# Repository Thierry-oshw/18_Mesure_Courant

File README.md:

# 18_Mesure_Courant
 Mesure courant 

Le module Mesure_courant permet de mesurer un courant sur circuit alternatif ou continu.
La tension sur la broche Imes est proportionnelle au courrant consommé par le circuit à raison de 0.066 V par ampère.
Il s'agit d'un capteur à effet Hall, il peut donc être perturbé si un champ magnétique est à proximité.

## Schéma

Plus d'information sur la [datasheet du Alegro ACS712](https://www.allegromicro.com/~/media/files/datasheets/acs712-datasheet.ashx).

## Fonctionnalités
- Petit (14,6x17,8 mm)
- Faible coût (2 couches avec composants d'un seul côté)
- Connecteur avec pas de 2.54 mm + empreinte crénelée pour connexion carte à carte

## Outils utilisés

- [Kicad V6](https://www.kicad.org/)

## Fabrication du circuit

Ce circuit a été testé de fond en comble sur de nombreux projets

## Contributeurs

- Thierry Orlandi ([Hardware Freelance](https://www.linkedin.com/in/thierry-orlandi))
- Yohann Belair ([R&D Freelance](https://github.com/ciborg971))

## Licence
[CERN Open Hardware Licence Version 2](https://github.com/Thierry-oshw/18_Mesure_Courant/blob/main/LICENSE.txt)

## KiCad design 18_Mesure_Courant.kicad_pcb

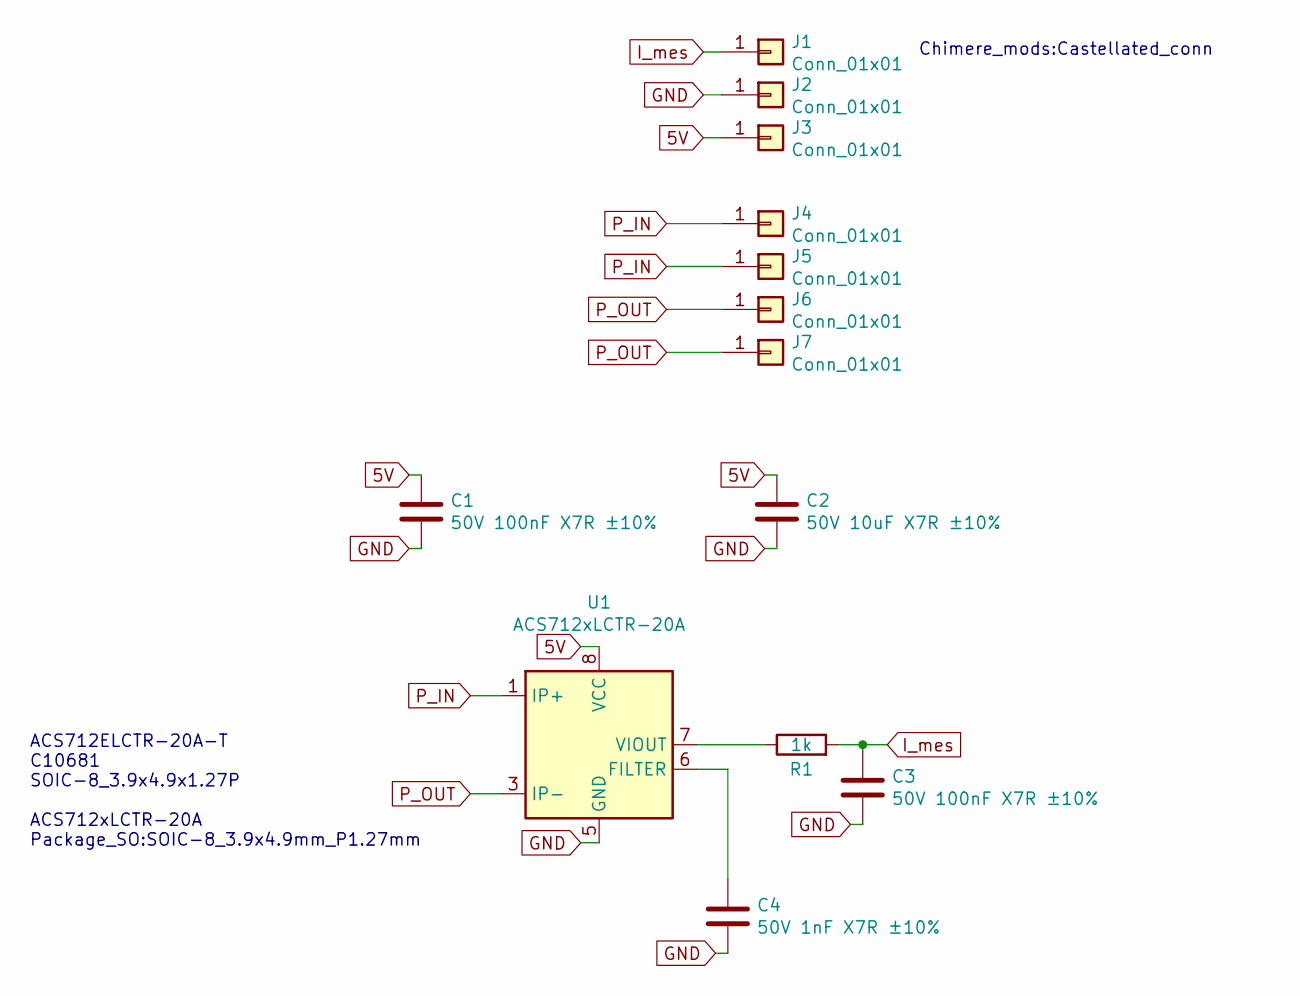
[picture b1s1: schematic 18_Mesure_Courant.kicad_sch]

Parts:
C1, C3: 50V 100nF X7R ±10%; C_0603_1608Metric; LCSC C14663
C2: 50V 10uF X7R ±10%; C_1210_3225Metric; LCSC C337485
C4: 50V 1nF X7R ±10%; C_0603_1608Metric; LCSC C1588
J1, J2, J3, J4, J5, J6, J7: Conn_01x01; Castellated_conn
R1: 1k; R_0603_1608Metric; LCSC C21190
U1: ACS712xLCTR-20A; SOIC-8_3.9x4.9mm_P1.27mm; LCSC C10681

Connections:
5V: C1.1, C2.1, J3.1, U1.8 (VCC)
GND: C1.2, C2.2, C3.2, C4.2, J2.1, U1.5 (GND)
I_mes: C3.1, J1.1, R1.2
unnamed: C4.1, U1.6 (FILTER)
unnamed: R1.1, U1.7 (VIOUT)
P_IN: J4.1, J5.1, U1.1 (IP+), U1.2 (IP+)
P_OUT: J6.1, J7.1, U1.3 (IP-), U1.4 (IP-)

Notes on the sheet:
ACS712ELCTR-20A-T C10681 SOIC-8_3.9x4.9x1.27P ACS712xLCTR-20A Package_SO:SOIC-8_3.9x4.9mm_P1.27mm
Chimere_mods:Castellated_conn

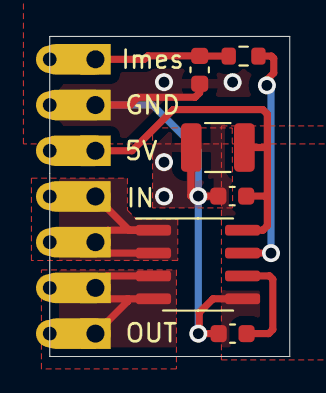
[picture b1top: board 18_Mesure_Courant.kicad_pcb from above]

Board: 2 copper layers, 13.3 x 17.8 mm, 13 parts (0 on the bottom side), 7 nets.

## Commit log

2021-06-01 schéma + routage
2021-07-26 maj split librairies
2023-05-02 chgt nom fichier licence
2023-05-02 maj kicad 6
2023-05-02 effacement fichiers obsoletes
2023-05-02 maj schéma
    symboles depuis librairies
    vérification empreintes
    ajout ligne LCSC
2023-05-02 maj pcb
    maj liens librairies
    maj empreinte
    maj modèles 3D
2023-05-02 mise en place et routage
2023-05-03 maj config gerbers
    génération des fichiers pour fabrication
    ajout ref lcsc pour R1
2023-05-03 création step
    création step
    chgt origine coordonnées
2023-05-09 maj chemin librairies
2023-05-28 maj readme
2023-05-28 maj readme : changement lien license
